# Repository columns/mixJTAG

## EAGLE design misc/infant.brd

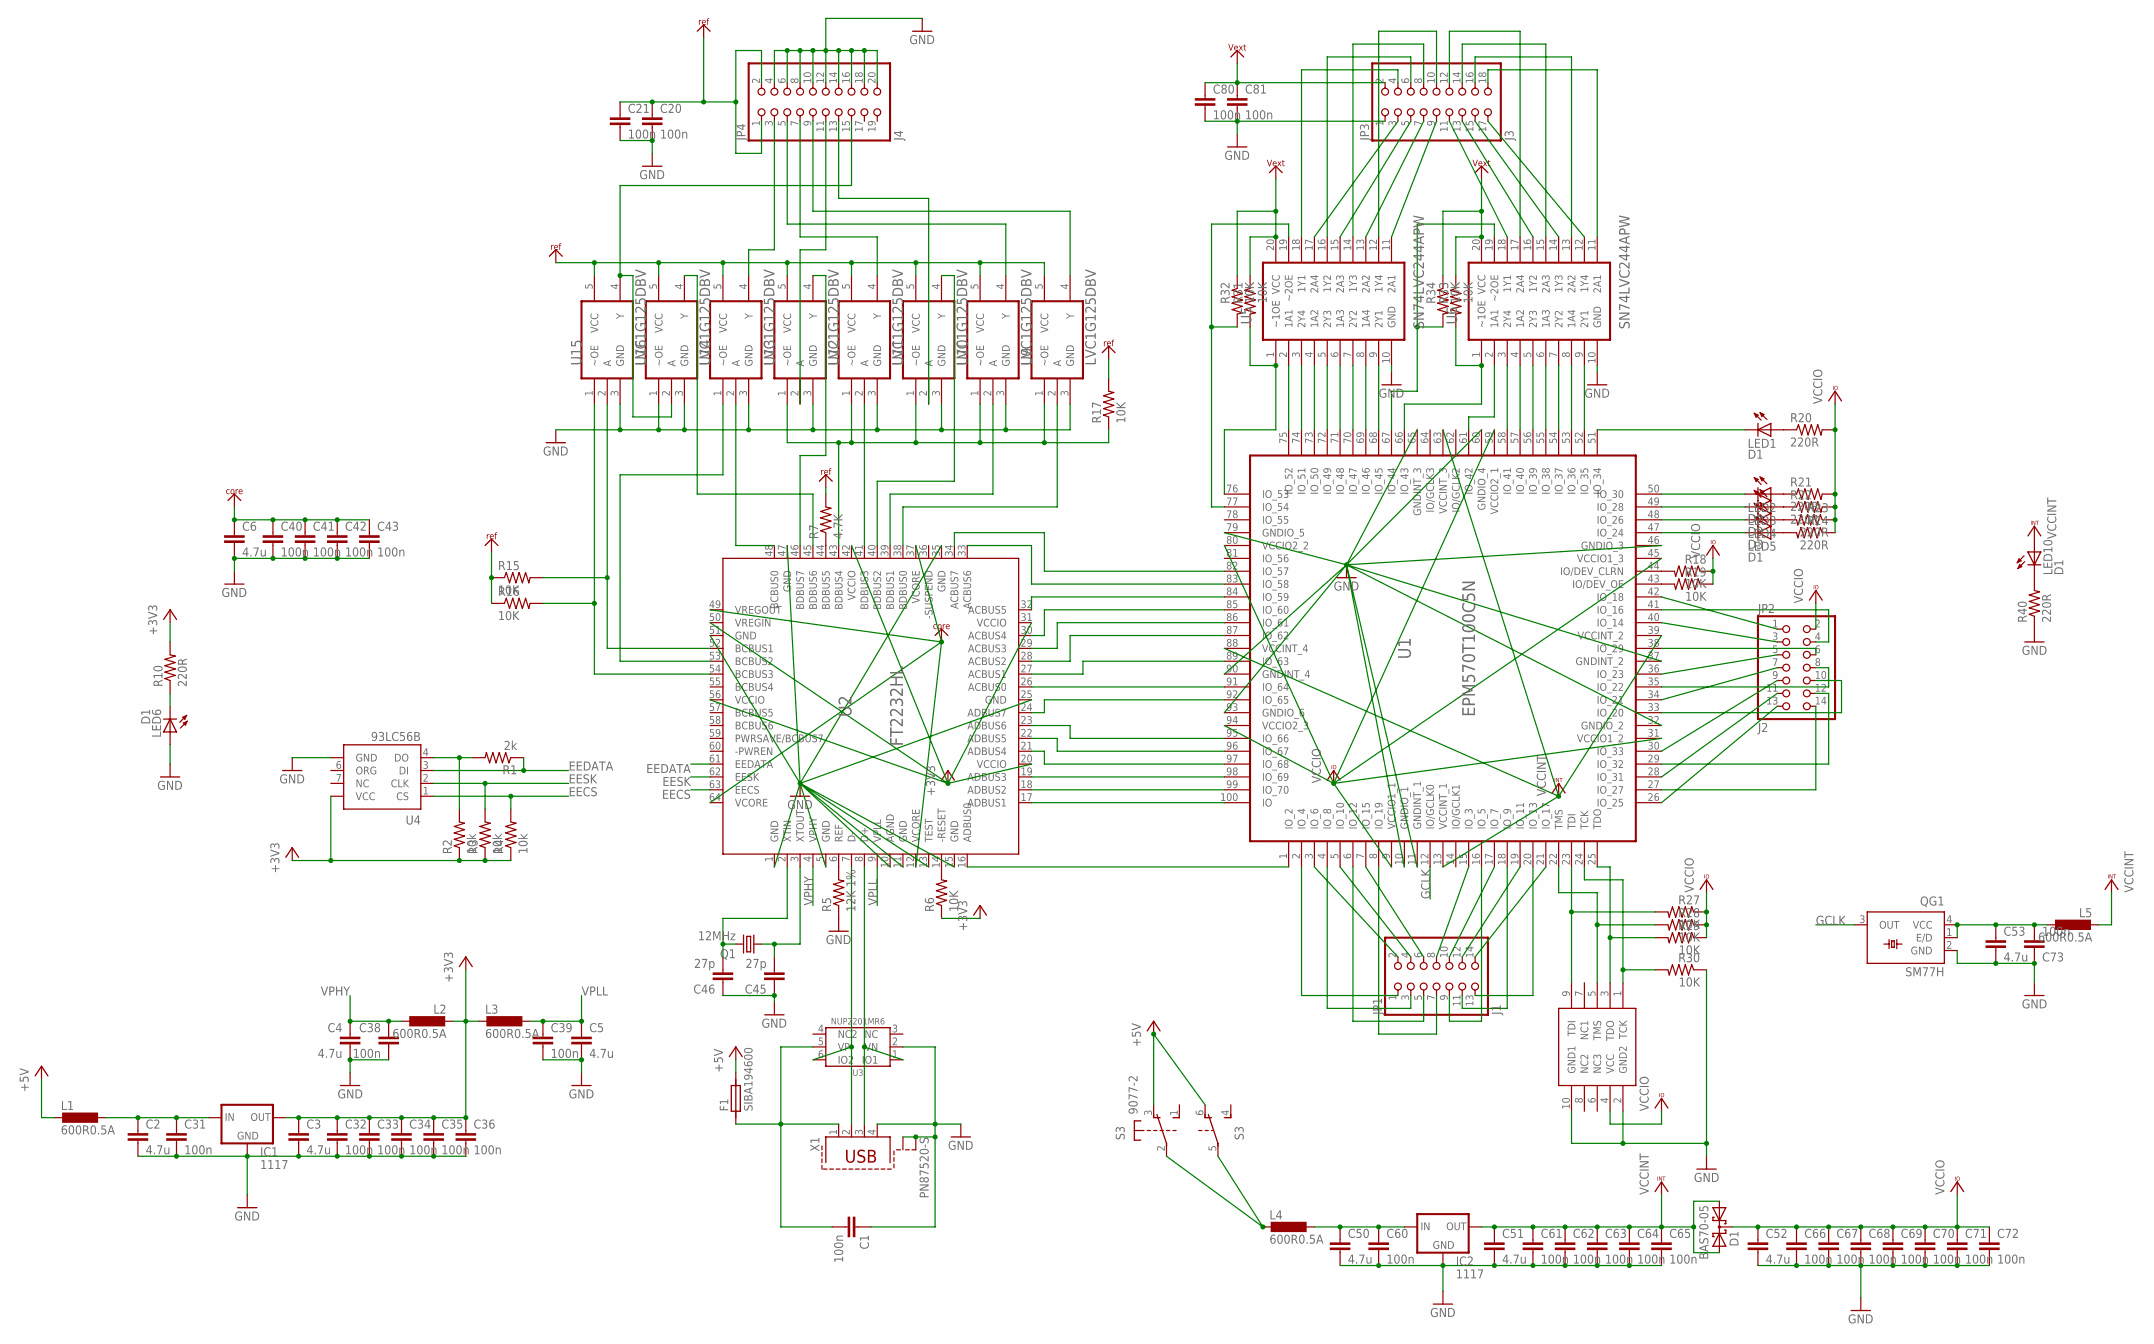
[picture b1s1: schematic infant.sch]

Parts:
C1, C20, C21, C31, C32, C33, C34, C35, C36, C38, C39, C40, C41, C42, C43, C60, C61, C62, C63, C64, C65, C66, C67, C68, C69, C70, C71, C72, C73, C80, C81: 100n; C0805
C2, C3, C4, C5, C6, C50, C51, C52, C53: 4.7u; C0805K
C45, C46: 27p; C025-025X050
D1: BAS70-05; SOT23
F1: SIBA194600; C1812
IC1, IC2: 1117; SOT223
JP1: J1; 2X07
JP2: J2; 2X07
JP3: J3; 2X09
JP4: J4; 2X10
L1, L2, L3, L4, L5: 600R0.5A; R0805
LED1, LED5, LED6, LED10: D1; CHIPLED_0805
LED2: D2; CHIPLED_0805
LED3, LED4: D3; CHIPLED_0805
Q1: 12MHz; HC49/S
QG1: SM77H
R1: 2k; R0805
R2, R3, R4: 10k; R0805
R5: 12K 1%; R0805
R6, R15, R16, R17, R18, R19, R27, R28, R29, R30, R31, R32, R33, R34: 10K; R0805
R7: 4.7K; R0805
R10, R20, R21, R22, R23, R24, R40: 220R; R0805
S3: 9077-2
U1: EPM570T100C5N; TQFP100
U2: FT2232HL; LQFP-64
U3: NUP2201MR6; TSOP6
U4: 93LC56B; SOIC8
U5, U6: SN74LVC244APW; TSSOP20
U9, U10, U11, U12, U13, U14, U15, U16: LVC1G125DBV; SOT23-5
U$2: BOXHEADER10JTAG; ML10
X1: PN87520-S; USB

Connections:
+3V3: C3.1, C32.1, C33.1, C34.1, C35.1, C36.1, IC1.2 (OUT), L2.1, L3.1, R2.1, R3.1, R4.1, R6.1, R10.2, U2.20 (VCCIO), U2.31 (VCCIO), U2.42 (VCCIO), U2.50 (VREGIN), U2.56 (VCCIO), U4.8 (VCC)
+5V: F1.2, L1.1, S3.3 (O), S3.6 (O)
EECS: R4.2, U2.63 (EECS), U4.1 (CS)
EEDATA: R1.1, U2.61 (EEDATA), U4.3 (DI)
EESK: R3.2, U2.62 (EESK), U4.2 (CLK)
GCLK: QG1.3 (OUT), U1.12 (IO/GCLK0)
GND: C1.1, C2.2, C3.2, C4.2, C5.2, C6.2, C20.2, C21.2, C31.2, C32.2, C33.2, C34.2, C35.2, C36.2, C38.2, C39.2, C40.2, C41.2, C42.2, C43.2, C45.1, C46.1, C50.2, C51.2, C52.2, C53.2, C60.2, C61.2, C62.2, C63.2, C64.2, C65.2, C66.2, C67.2, C68.2, C69.2, C70.2, C71.2, C72.2, C73.1, C80.2, C81.2, IC1.1 (GND), IC2.1 (GND), JP3.1, JP4.4, JP4.6, JP4.8, JP4.10, JP4.12, JP4.14, JP4.16, JP4.18, JP4.20, LED6.A, QG1.2 (GND), R5.1, R30.1, R40.1, U1.10 (GNDIO_1), U1.11 (GNDINT_1), U1.32 (GNDIO_2), U1.37 (GNDINT_2), U1.46 (GNDIO_3), U1.60 (GNDIO_4), U1.65 (GNDINT_3), U1.79 (GNDIO_5), U1.90 (GNDINT_4), U1.93 (GNDIO_6), U2.1 (GND), U2.5 (GND), U2.10 (AGND), U2.11 (GND), U2.13 (TEST), U2.15 (GND), U2.25 (GND), U2.35 (GND), U2.47 (GND), U2.51 (GND), U3.2 (VN), U4.5 (GND), U5.10 (GND), U6.10 (GND), U9.3 (GND), U10.3 (GND), U11.3 (GND), U12.3 (GND), U13.3 (GND), U14.3 (GND), U15.3 (GND), U16.1 (~OE), U16.3 (GND), U$2.2 (GND2), U$2.10 (GND1), X1.4, X1.S1, X1.S2
unnamed: U2.7 (D-), U3.6 (IO2), X1.2
unnamed: U2.8 (D+), U3.1 (IO1), X1.3
unnamed: C2.1, C31.1, IC1.3 (IN), L1.2
unnamed: C46.2, Q1.2, U2.2 (XTIN)
unnamed: C45.2, Q1.1, U2.3 (XTOUT)
unnamed: U1.1 (IO_2), U2.16 (ADBUS0)
unnamed: U1.100 (IO), U2.17 (ADBUS1)
unnamed: U1.99 (IO_70), U2.18 (ADBUS2)
unnamed: U1.98 (IO_69), U2.19 (ADBUS3)
unnamed: U1.97 (IO_68), U2.21 (ADBUS4)
unnamed: U1.96 (IO_67), U2.22 (ADBUS5)
unnamed: U1.95 (IO_66), U2.23 (ADBUS6)
unnamed: R1.2, R2.2, U4.4 (DO)
unnamed: U1.92 (IO_65), U2.24 (ADBUS7)
unnamed: R5.2, U2.6 (REF)
unnamed: U1.91 (IO_64), U2.26 (ACBUS0)
unnamed: C50.1, C60.1, IC2.3 (IN), L4.2
unnamed: LED3.A, R22.1
unnamed: LED2.A, R21.1
unnamed: C53.1, C73.2, L5.2, QG1.1 (E/D), QG1.4 (VCC)
unnamed: LED1.A, R20.1
unnamed: U1.89 (IO_63), U2.27 (ACBUS1)
unnamed: U1.87 (IO_62), U2.28 (ACBUS2)
unnamed: U1.86 (IO_61), U2.29 (ACBUS3)
unnamed: R6.2, U2.14 (-RESET)
unnamed: U2.38 (BDBUS0), U9.2 (A)
unnamed: U1.85 (IO_60), U2.30 (ACBUS4)
unnamed: U1.84 (IO_59), U2.32 (ACBUS5)
unnamed: U2.39 (BDBUS1), U10.2 (A)
unnamed: U1.83 (IO_58), U2.33 (ACBUS6)
unnamed: U2.41 (BDBUS3), U12.2 (A)
unnamed: U1.82 (IO_57), U2.34 (ACBUS7)
unnamed: U1.52 (IO_35), U6.9 (2Y1)
unnamed: U1.53 (IO_36), U6.8 (1A4)
unnamed: U1.54 (IO_37), U6.7 (2Y2)
unnamed: U1.55 (IO_38), U6.6 (1A3)
unnamed: U1.56 (IO_39), U6.5 (2Y3)
unnamed: U1.57 (IO_40), U6.4 (1A2)
unnamed: U1.58 (IO_41), U6.3 (2Y4)
unnamed: U1.61 (IO_42), U6.2 (1A1)
unnamed: R33.2, U1.66 (IO_43), U6.1 (~1OE)
unnamed: R34.2, U1.67 (IO_44), U6.19 (~2OE)
unnamed: U1.68 (IO_45), U5.9 (2Y1)
unnamed: U1.69 (IO_46), U5.8 (1A4)
unnamed: U1.70 (IO_47), U5.7 (2Y2)
unnamed: U1.71 (IO_48), U5.6 (1A3)
unnamed: U1.72 (IO_49), U5.5 (2Y3)
unnamed: U1.73 (IO_50), U5.4 (1A2)
unnamed: U1.74 (IO_51), U5.3 (2Y4)
unnamed: U1.75 (IO_52), U5.2 (1A1)
unnamed: R31.2, U1.76 (IO_53), U5.1 (~1OE)
unnamed: R32.2, U1.77 (IO_54), U5.19 (~2OE)
unnamed: U2.40 (BDBUS2), U11.4 (Y)
unnamed: R15.2, U2.52 (BCBUS1), U15.2 (A)
unnamed: U2.48 (BCBUS0), U14.2 (A)
unnamed: U2.53 (BCBUS2), U14.1 (~OE)
unnamed: R16.2, U2.54 (BCBUS3), U15.1 (~OE)
unnamed: U2.46 (BDBUS7), U13.4 (Y)
unnamed: U2.45 (BDBUS6), U16.4 (Y)
unnamed: LED4.A, R23.2
unnamed: LED2.C, U1.50 (IO_30)
unnamed: LED3.C, U1.49 (IO_28)
unnamed: L4.1, S3.2, S3.5
unnamed: LED4.C, U1.48 (IO_26)
unnamed: JP2.14, U1.27 (IO_27)
unnamed: R27.2, U1.23 (TDI), U$2.9 (TDI)
unnamed: R28.2, U1.22 (TMS), U$2.5 (TMS)
unnamed: R30.2, U1.24 (TCK), U$2.1 (TCK)
unnamed: R29.2, U1.25 (TDO), U$2.3 (TDO)
unnamed: JP2.1, U1.42 (IO_18)
unnamed: JP2.3, U1.40 (IO_14)
unnamed: JP3.9, U5.11 (2A1)
unnamed: JP3.7, U5.13 (2A2)
unnamed: JP3.5, U5.15 (2A3)
unnamed: JP3.3, U5.17 (2A4)
unnamed: JP3.11, U6.18 (1Y1)
unnamed: JP3.13, U6.16 (1Y2)
unnamed: JP3.15, U6.14 (1Y3)
unnamed: JP3.17, U6.12 (1Y4)
unnamed: JP3.4, U5.18 (1Y1)
unnamed: JP3.6, U5.16 (1Y2)
unnamed: JP3.8, U5.14 (1Y3)
unnamed: JP3.10, U5.12 (1Y4)
unnamed: JP3.12, U6.17 (2A4)
unnamed: JP3.14, U6.15 (2A3)
unnamed: JP3.16, U6.13 (2A2)
unnamed: JP3.18, U6.11 (2A1)
unnamed: JP2.12, U1.29 (IO_32)
unnamed: JP2.13, U1.26 (IO_25)
unnamed: JP2.11, U1.28 (IO_31)
unnamed: JP2.10, U1.33 (IO_20)
unnamed: R18.2, U1.44 (IO/DEV_CLRN)
unnamed: R19.2, U1.43 (IO/DEV_OE)
unnamed: JP2.5, U1.36 (IO_23)
unnamed: JP2.9, U1.30 (IO_33)
unnamed: JP2.8, U1.35 (IO_22)
unnamed: JP2.7, U1.34 (IO_21)
unnamed: JP2.4, U1.41 (IO_16)
unnamed: JP2.6, U1.38 (IO_29)
unnamed: LED5.A, R24.2
unnamed: JP1.1, U1.2 (IO_4)
unnamed: JP1.2, U1.3 (IO_6)
unnamed: JP1.3, U1.4 (IO_8)
unnamed: JP1.8, U1.15 (IO_3)
unnamed: JP1.6, U1.7 (IO_15)
unnamed: JP1.10, U1.17 (IO_7)
unnamed: JP1.12, U1.19 (IO_11)
unnamed: JP1.7, U1.8 (IO_19)
unnamed: JP1.14, U1.21 (IO_17)
unnamed: JP1.13, U1.20 (IO_13)
unnamed: JP1.5, U1.6 (IO_12)
unnamed: JP1.11, U1.18 (IO_9)
unnamed: JP1.9, U1.16 (IO_5)
unnamed: JP1.4, U1.5 (IO_10)
unnamed: R7.1, U2.44 (BDBUS5)
unnamed: JP4.11, U13.2 (A)
unnamed: JP4.5, U10.4 (Y)
unnamed: JP4.3, U14.4 (Y)
unnamed: LED5.C, U1.47 (IO_24)
unnamed: JP4.9, U9.4 (Y)
unnamed: JP4.7, U12.4 (Y)
unnamed: JP4.13, U11.2 (A)
unnamed: JP4.15, U15.4 (Y), U16.2 (A)
unnamed: R17.1, U2.43 (BDBUS4), U9.1 (~OE), U10.1 (~OE), U11.1 (~OE), U12.1 (~OE), U13.1 (~OE)
unnamed: C1.2, F1.1, U3.5 (VP), X1.1
unnamed: LED10.C, R40.2
unnamed: LED1.C, U1.51 (IO_34)
unnamed: LED6.C, R10.1
VCC: C20.1, C21.1, JP4.1, JP4.2, R7.2, R15.1, R16.1, R17.2, U9.5 (VCC), U10.5 (VCC), U11.5 (VCC), U12.5 (VCC), U13.5 (VCC), U14.5 (VCC), U15.5 (VCC), U16.5 (VCC)
VCCINT: C51.1, C61.1, C62.1, C63.1, C64.1, C65.1, D1.1 (A1), D1.2 (A2), IC2.2 (OUT), L5.1, LED10.A, U1.13 (VCCINT_1), U1.39 (VCCINT_2), U1.63 (VCCINT_3), U1.88 (VCCINT_4)
VCCIO: C52.1, C66.1, C67.1, C68.1, C69.1, C70.1, C71.1, C72.1, D1.3 (C), JP2.2, R18.1, R19.1, R20.2, R21.2, R22.2, R23.1, R24.1, R27.1, R28.1, R29.1, U1.9 (VCCIO1_1), U1.31 (VCCIO1_2), U1.45 (VCCIO1_3), U1.59 (VCCIO2_1), U1.80 (VCCIO2_2), U1.94 (VCCIO2_3), U$2.4 (VCC)
VCORE: C6.1, C40.1, C41.1, C42.1, C43.1, U2.12 (VCORE), U2.37 (VCORE), U2.49 (VREGOUT), U2.64 (VCORE)
VEXT: C80.1, C81.1, JP3.2, R31.1, R32.1, R33.1, R34.1, U5.20 (VCC), U6.20 (VCC)
VPHY: C4.1, C38.1, L2.2, U2.4 (VPHY)
VPLL: C5.1, C39.1, L3.2, U2.9 (VPLL)

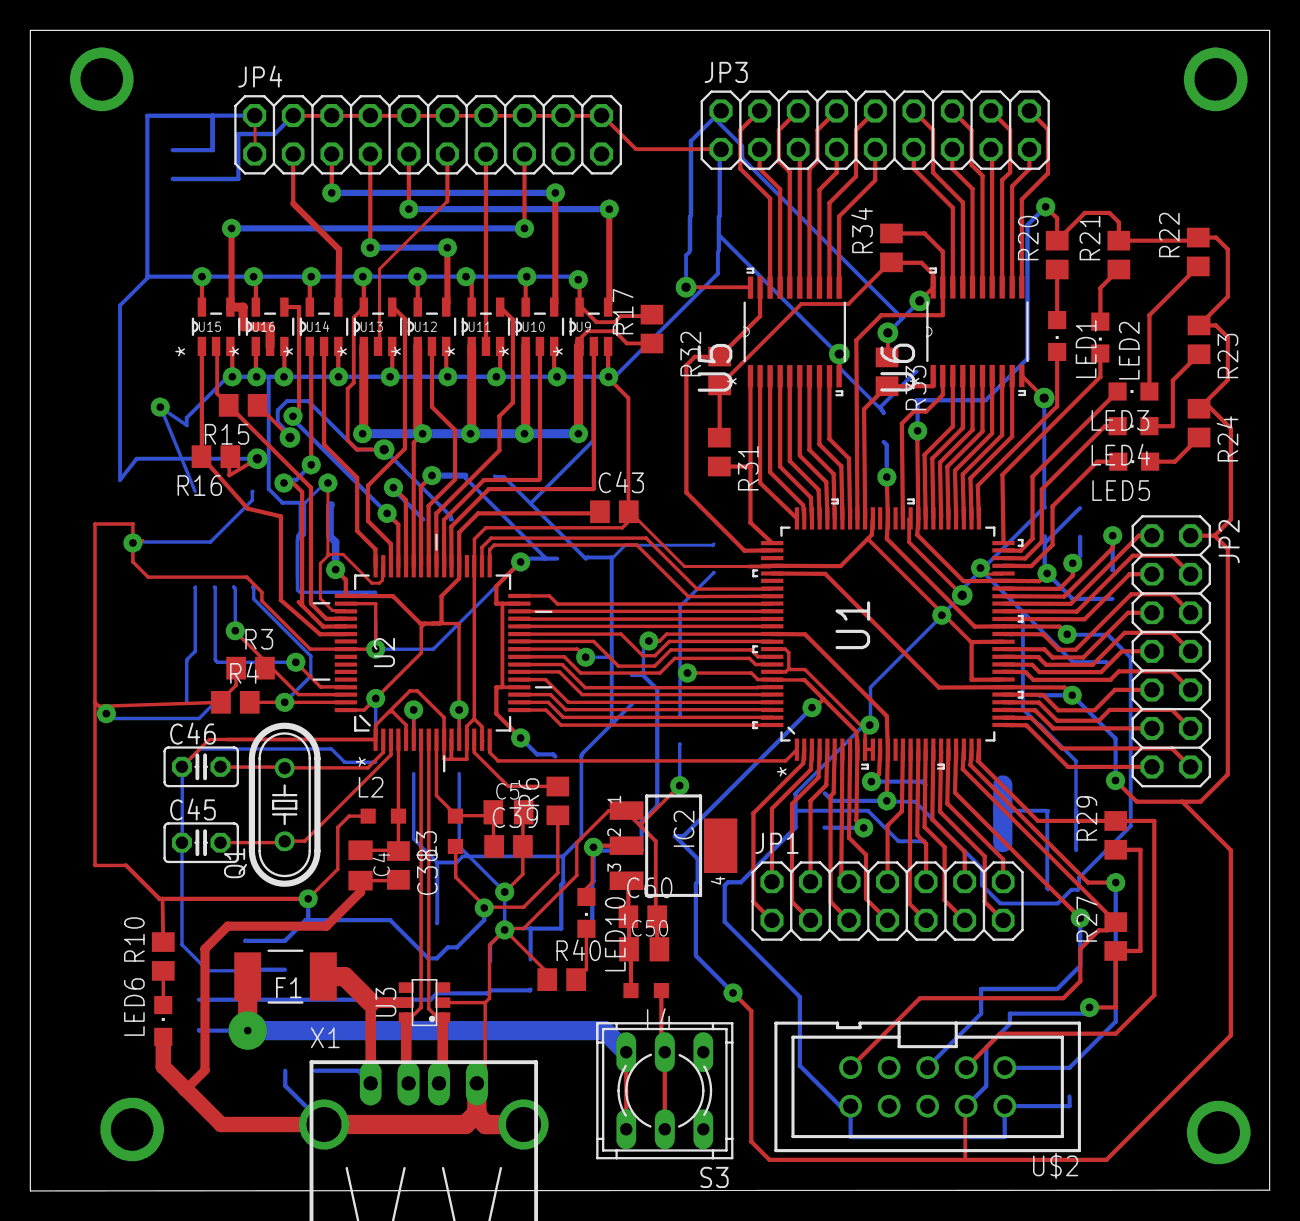
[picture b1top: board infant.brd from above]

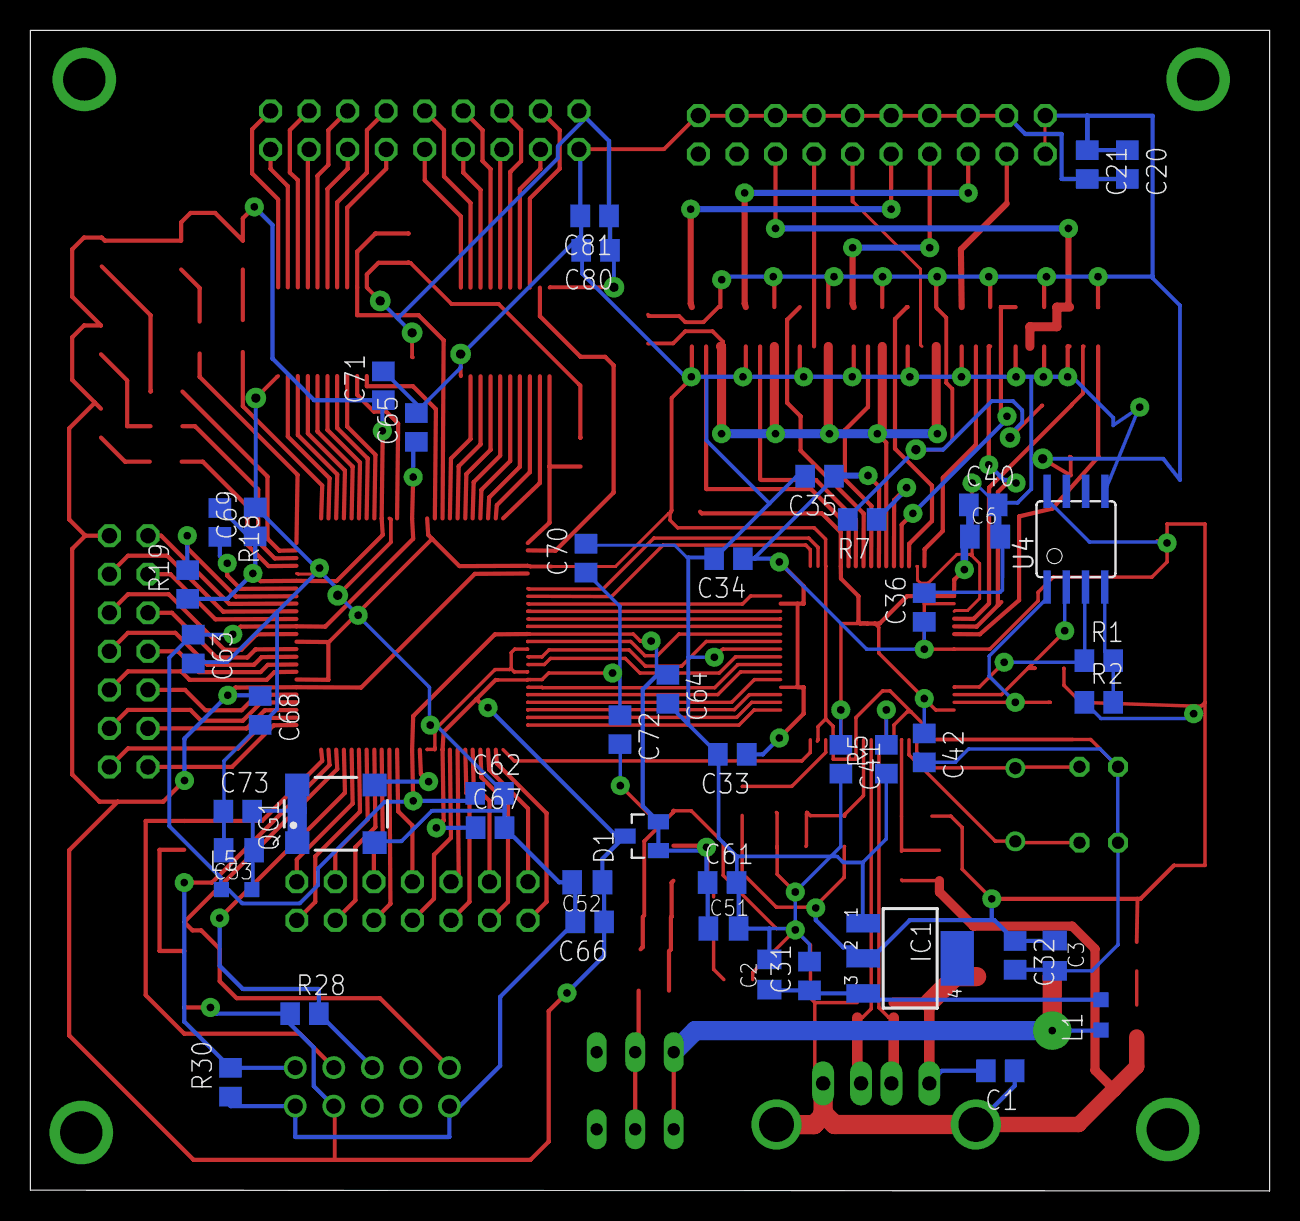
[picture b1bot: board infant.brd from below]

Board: 2 copper layers, 81.7 x 76.5 mm, 108 parts (47 on the bottom side), 142 nets.

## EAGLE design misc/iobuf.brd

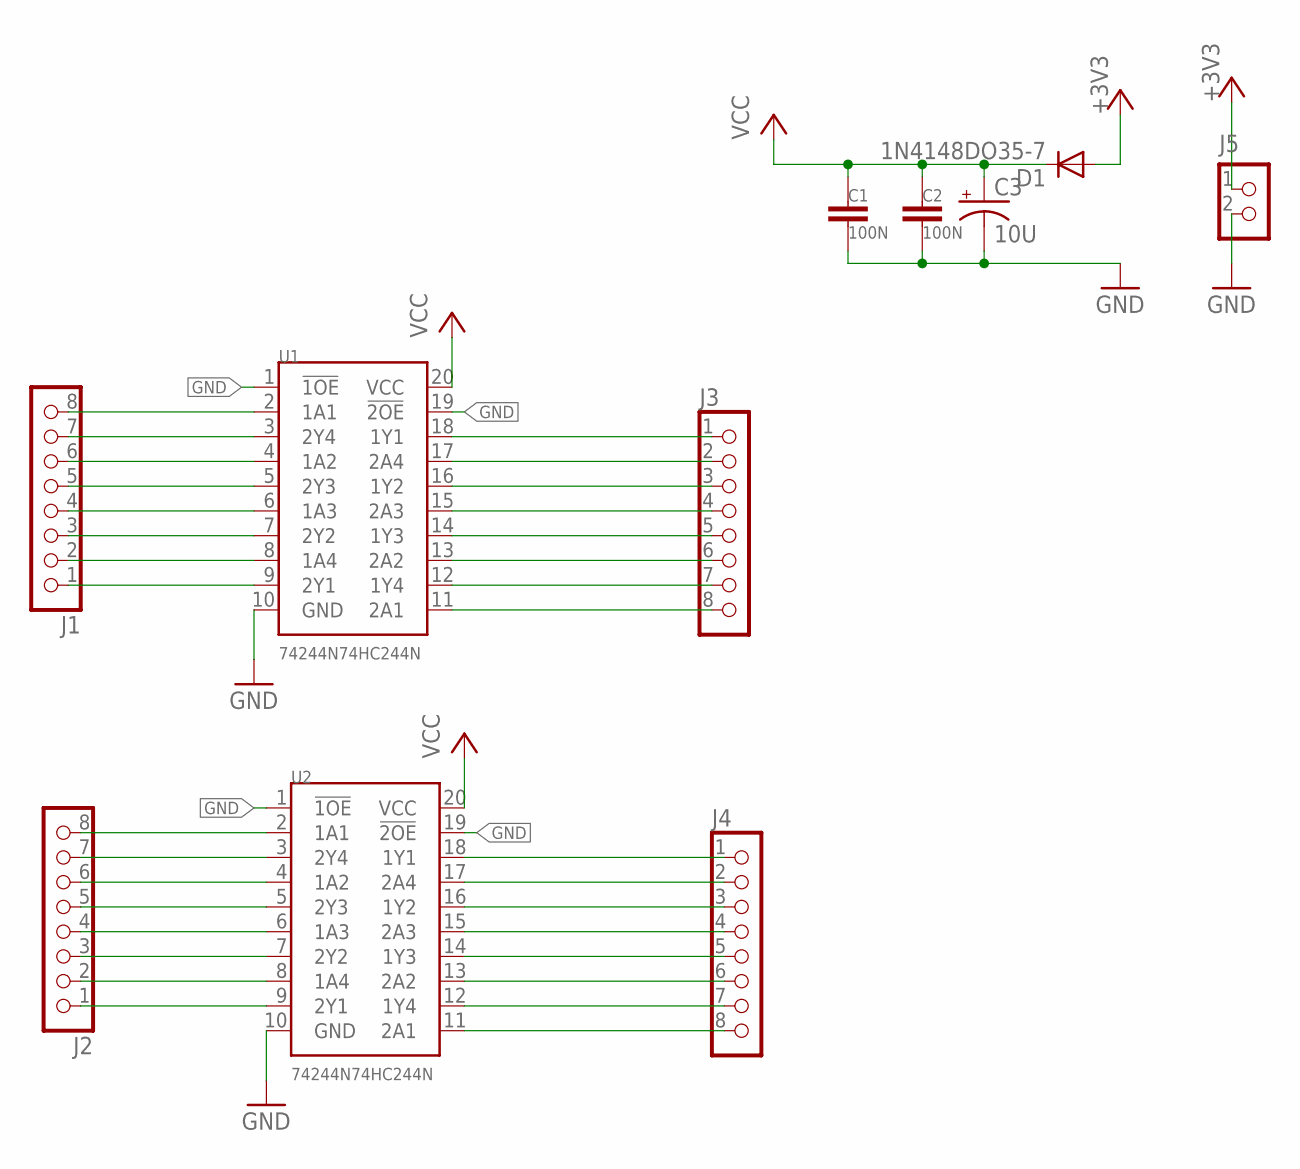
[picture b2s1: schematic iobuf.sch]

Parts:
C1, C2: 100N; C025-025X050
C3: 10U; E2,5-7
D1: 1N4148DO35-7; DO35-7
J1, J2, J3, J4: CON_HEADER_1X08-PTH; M1X8
J5: CON_HEADER_1X02-PTH; M1X2
U1, U2: 74244N74HC244N; DIL20

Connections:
+3V3: D1.A, J5.1
GND: C1.2, C2.2, C3.-, J5.2, U1.1 (!1OE), U1.10 (GND), U1.19 (!2OE), U2.1 (!1OE), U2.10 (GND), U2.19 (!2OE)
unnamed: J1.1, U1.9 (2Y1)
unnamed: J1.2, U1.8 (1A4)
unnamed: J1.3, U1.7 (2Y2)
unnamed: J1.4, U1.6 (1A3)
unnamed: J1.5, U1.5 (2Y3)
unnamed: J1.6, U1.4 (1A2)
unnamed: J1.7, U1.3 (2Y4)
unnamed: J1.8, U1.2 (1A1)
unnamed: J3.8, U1.11 (2A1)
unnamed: J3.7, U1.12 (1Y4)
unnamed: J3.6, U1.13 (2A2)
unnamed: J3.5, U1.14 (1Y3)
unnamed: J3.4, U1.15 (2A3)
unnamed: J3.3, U1.16 (1Y2)
unnamed: J3.2, U1.17 (2A4)
unnamed: J3.1, U1.18 (1Y1)
unnamed: J2.1, U2.9 (2Y1)
unnamed: J2.2, U2.8 (1A4)
unnamed: J2.3, U2.7 (2Y2)
unnamed: J2.4, U2.6 (1A3)
unnamed: J2.5, U2.5 (2Y3)
unnamed: J2.6, U2.4 (1A2)
unnamed: J2.7, U2.3 (2Y4)
unnamed: J2.8, U2.2 (1A1)
unnamed: J4.8, U2.11 (2A1)
unnamed: J4.7, U2.12 (1Y4)
unnamed: J4.6, U2.13 (2A2)
unnamed: J4.5, U2.14 (1Y3)
unnamed: J4.4, U2.15 (2A3)
unnamed: J4.3, U2.16 (1Y2)
unnamed: J4.2, U2.17 (2A4)
unnamed: J4.1, U2.18 (1Y1)
VCC: C1.1, C2.1, C3.+, D1.C, U1.20 (VCC), U2.20 (VCC)

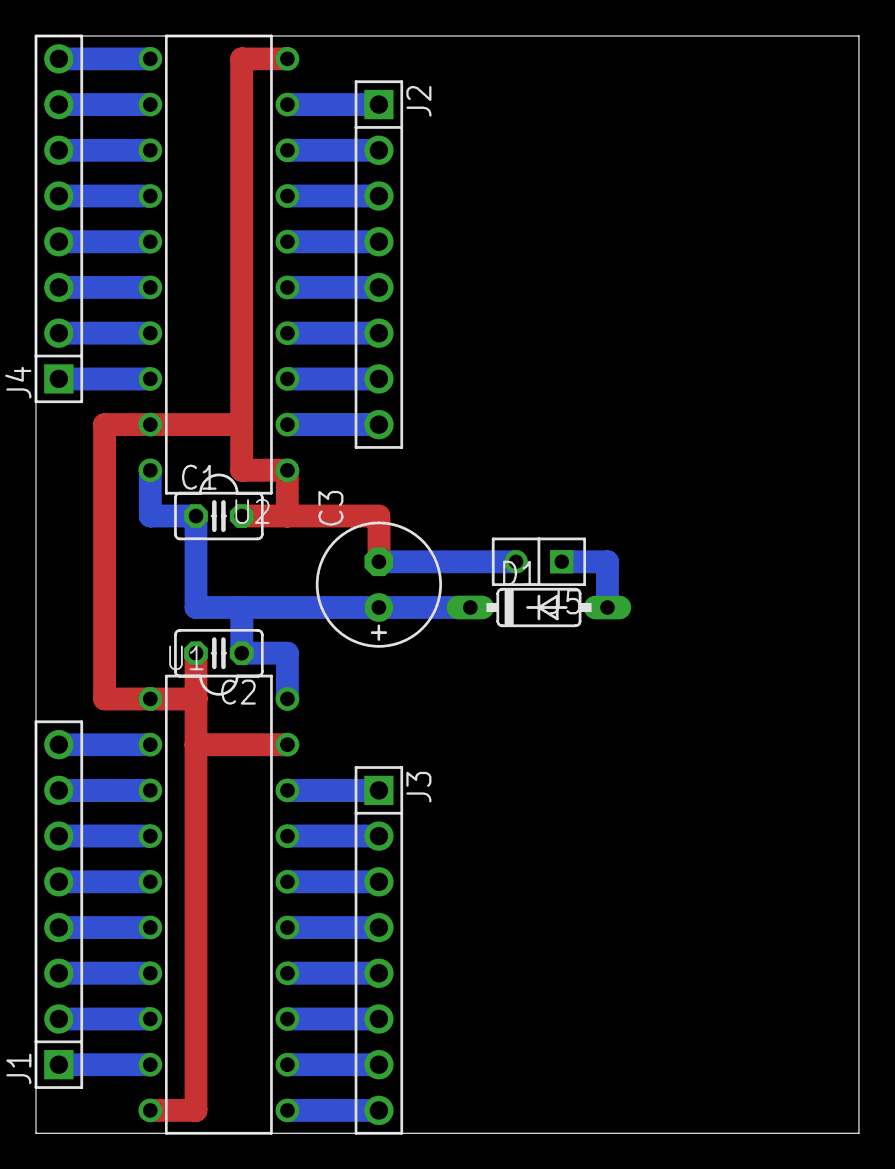
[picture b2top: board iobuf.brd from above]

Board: 2 copper layers, 45.7 x 61.0 mm, 11 parts (0 on the bottom side), 35 nets.

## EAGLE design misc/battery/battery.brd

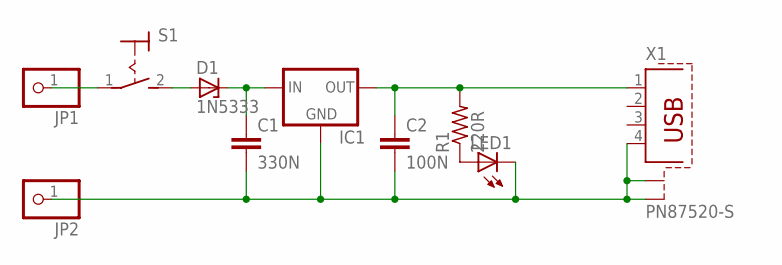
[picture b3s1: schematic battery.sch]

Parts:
C1: 330N; C025-025X050
C2: 100N; C025-025X050
D1: 1N5333; C1702-15
IC1: 78MXXS
JP1, JP2: PINHD-1X1; 1X01
LED1: LED3MM
R1: 220R; 0414/15
S1: MS243
X1: PN87520-S

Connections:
unnamed: LED1.A, R1.1
unnamed: C1.2, C2.2, IC1.GND, JP2.1, LED1.K (C), X1.4, X1.S1, X1.S2
unnamed: JP1.1, S1.1
unnamed: C1.1, D1.C, IC1.IN
unnamed: C2.1, IC1.OUT, R1.2, X1.1
unnamed: D1.A, S1.2 (S)

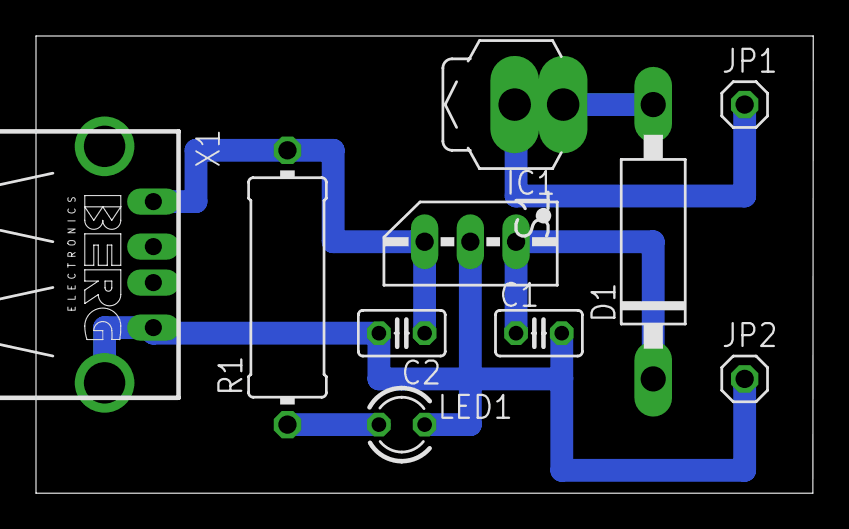
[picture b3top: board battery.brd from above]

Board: 2 copper layers, 43.2 x 25.4 mm, 10 parts (0 on the bottom side), 6 nets.

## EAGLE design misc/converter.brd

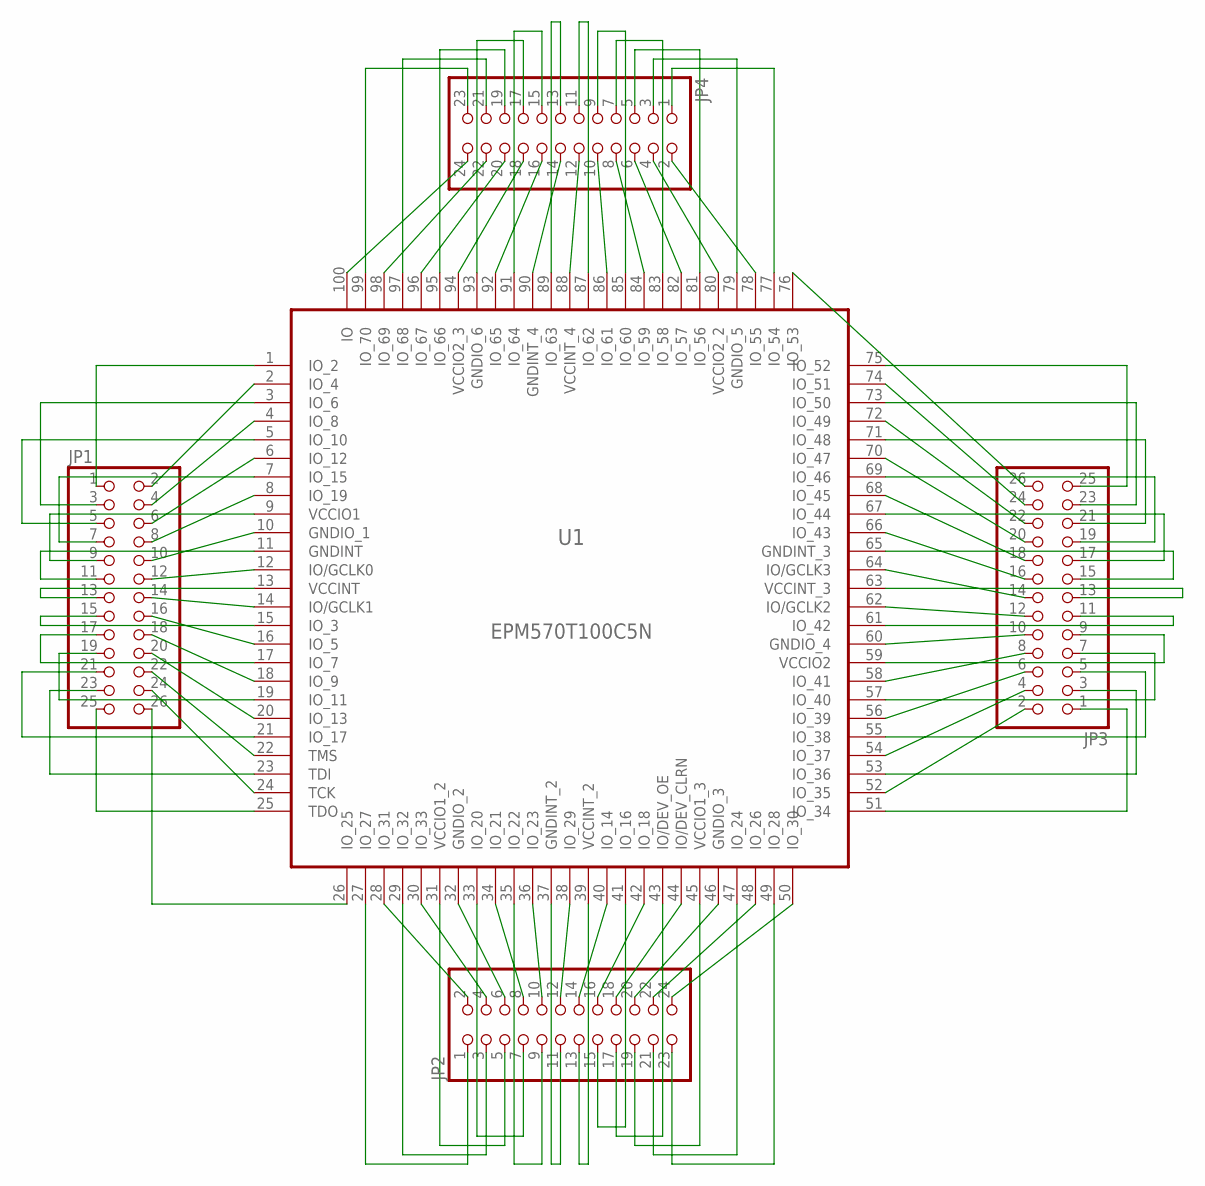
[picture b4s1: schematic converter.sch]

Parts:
JP1, JP3: PINHD-2X13; 2X13
JP2, JP4: PINHD-2X12; 2X12
U1: EPM570T100C5N; QFP50P1600X1600X120-100N

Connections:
unnamed: JP1.1, U1.1 (IO_2)
unnamed: JP1.2, U1.2 (IO_4)
unnamed: JP1.3, U1.3 (IO_6)
unnamed: JP1.4, U1.4 (IO_8)
unnamed: JP1.5, U1.5 (IO_10)
unnamed: JP1.6, U1.6 (IO_12)
unnamed: JP1.7, U1.7 (IO_15)
unnamed: JP1.8, U1.8 (IO_19)
unnamed: JP1.9, U1.9 (VCCIO1)
unnamed: JP1.10, U1.10 (GNDIO_1)
unnamed: JP1.11, U1.11 (GNDINT)
unnamed: JP1.13, U1.13 (VCCINT)
unnamed: JP1.14, U1.14 (IO/GCLK1)
unnamed: JP1.15, U1.15 (IO_3)
unnamed: JP1.16, U1.16 (IO_5)
unnamed: JP1.17, U1.17 (IO_7)
unnamed: JP1.18, U1.18 (IO_9)
unnamed: JP1.19, U1.19 (IO_11)
unnamed: JP1.20, U1.20 (IO_13)
unnamed: JP1.21, U1.21 (IO_17)
unnamed: JP1.22, U1.22 (TMS)
unnamed: JP1.23, U1.23 (TDI)
unnamed: JP1.24, U1.24 (TCK)
unnamed: JP1.25, U1.25 (TDO)
unnamed: JP1.26, U1.26 (IO_25)
unnamed: JP2.1, U1.27 (IO_27)
unnamed: JP2.2, U1.28 (IO_31)
unnamed: JP2.3, U1.29 (IO_32)
unnamed: JP2.4, U1.30 (IO_33)
unnamed: JP2.5, U1.31 (VCCIO1_2)
unnamed: JP2.6, U1.32 (GNDIO_2)
unnamed: JP2.7, U1.33 (IO_20)
unnamed: JP2.8, U1.34 (IO_21)
unnamed: JP2.9, U1.35 (IO_22)
unnamed: JP2.10, U1.36 (IO_23)
unnamed: JP2.11, U1.37 (GNDINT_2)
unnamed: JP2.12, U1.38 (IO_29)
unnamed: JP2.13, U1.39 (VCCINT_2)
unnamed: JP2.15, U1.41 (IO_16)
unnamed: JP2.16, U1.42 (IO_18)
unnamed: JP2.17, U1.43 (IO/DEV_OE)
unnamed: JP2.18, U1.44 (IO/DEV_CLRN)
unnamed: JP2.19, U1.45 (VCCIO1_3)
unnamed: JP2.20, U1.46 (GNDIO_3)
unnamed: JP2.21, U1.47 (IO_24)
unnamed: JP2.22, U1.48 (IO_26)
unnamed: JP2.23, U1.49 (IO_28)
unnamed: JP2.24, U1.50 (IO_30)
unnamed: JP3.1, U1.51 (IO_34)
unnamed: JP3.2, U1.52 (IO_35)
unnamed: JP3.3, U1.53 (IO_36)
unnamed: JP3.4, U1.54 (IO_37)
unnamed: JP3.5, U1.55 (IO_38)
unnamed: JP3.6, U1.56 (IO_39)
unnamed: JP3.7, U1.57 (IO_40)
unnamed: JP3.8, U1.58 (IO_41)
unnamed: JP3.9, U1.59 (VCCIO2)
unnamed: JP3.10, U1.60 (GNDIO_4)
unnamed: JP3.11, U1.61 (IO_42)
unnamed: JP3.12, U1.62 (IO/GCLK2)
unnamed: JP3.13, U1.63 (VCCINT_3)
unnamed: JP3.14, U1.64 (IO/GCLK3)
unnamed: JP3.15, U1.65 (GNDINT_3)
unnamed: JP3.16, U1.66 (IO_43)
unnamed: JP3.17, U1.67 (IO_44)
unnamed: JP3.19, U1.69 (IO_46)
unnamed: JP3.20, U1.70 (IO_47)
unnamed: JP3.21, U1.71 (IO_48)
unnamed: JP3.22, U1.72 (IO_49)
unnamed: JP3.23, U1.73 (IO_50)
unnamed: JP3.24, U1.74 (IO_51)
unnamed: JP3.25, U1.75 (IO_52)
unnamed: JP3.26, U1.76 (IO_53)
unnamed: JP4.1, U1.77 (IO_54)
unnamed: JP4.2, U1.78 (IO_55)
unnamed: JP4.3, U1.79 (GNDIO_5)
unnamed: JP4.4, U1.80 (VCCIO2_2)
unnamed: JP4.5, U1.81 (IO_56)
unnamed: JP4.6, U1.82 (IO_57)
unnamed: JP4.7, U1.83 (IO_58)
unnamed: JP4.8, U1.84 (IO_59)
unnamed: JP4.9, U1.85 (IO_60)
unnamed: JP4.10, U1.86 (IO_61)
unnamed: JP4.11, U1.87 (IO_62)
unnamed: JP4.12, U1.88 (VCCINT_4)
unnamed: JP4.13, U1.89 (IO_63)
unnamed: JP4.15, U1.91 (IO_64)
unnamed: JP4.16, U1.92 (IO_65)
unnamed: JP4.17, U1.93 (GNDIO_6)
unnamed: JP4.18, U1.94 (VCCIO2_3)
unnamed: JP4.19, U1.95 (IO_66)
unnamed: JP4.20, U1.96 (IO_67)
unnamed: JP4.21, U1.97 (IO_68)
unnamed: JP4.22, U1.98 (IO_69)
unnamed: JP4.23, U1.99 (IO_70)
unnamed: JP4.24, U1.100 (IO)
unnamed: JP1.12, U1.12 (IO/GCLK0)
unnamed: JP2.14, U1.40 (IO_14)
unnamed: JP3.18, U1.68 (IO_45)
unnamed: JP4.14, U1.90 (GNDINT_4)

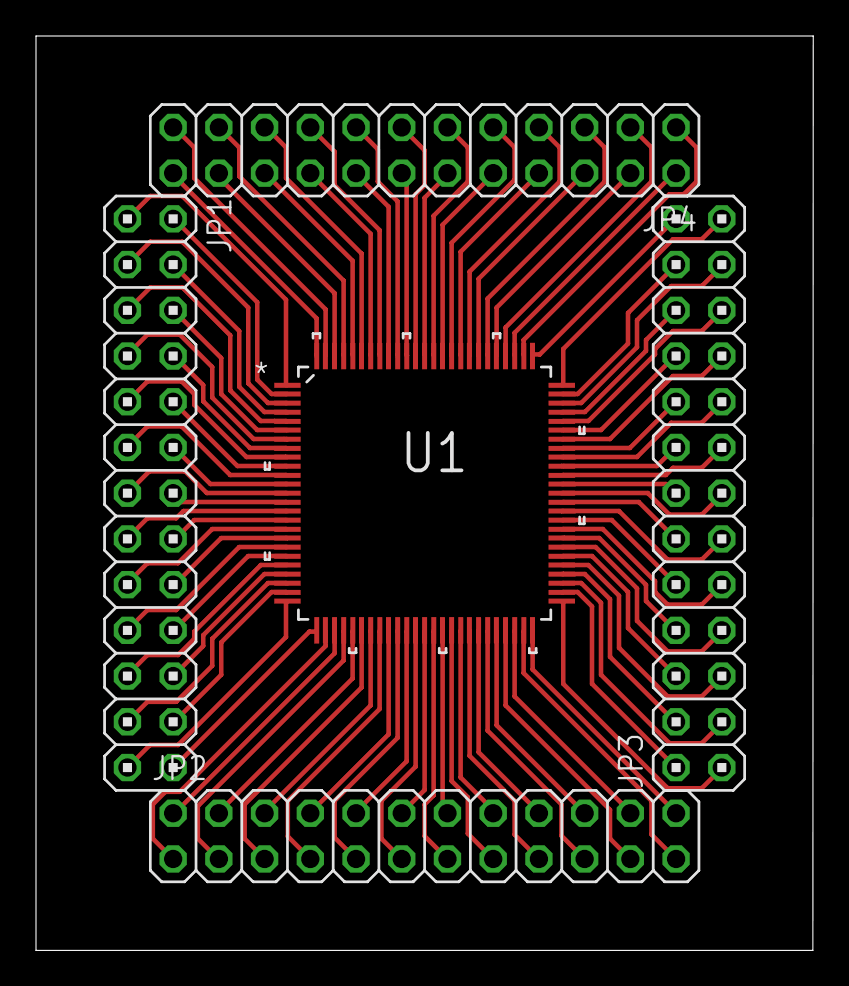
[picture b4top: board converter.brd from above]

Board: 2 copper layers, 43.2 x 50.8 mm, 5 parts (0 on the bottom side), 100 nets.
